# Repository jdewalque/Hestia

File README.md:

# Hestia

Bijou connecté avec bouton d'urgence : une pression envoie la position du
porteur par SMS à ses contacts. Prototype sur Thingy:91 X.

- `docs/architecture.md` — **à lire en premier** : architecture, fonctionnement
  et fonctionnalités, en résumé.
- `app/` — application mobile (Flutter, Android et iPhone) pour régler le bijou.
- `firmware/` — firmware du bijou pour le Thingy:91 X (voir `firmware/README.md`).
- `server/` — serveur qui transforme les alertes reçues par nRF Cloud en SMS
  (voir `server/README.md`).
- `docs/protocole-ble.md` — dialogue entre l'application et le bijou.
- `docs/consommation.md` — consommation estimée et autonomie du bijou.

## Application

L'application permet de relier le bijou au téléphone, de choisir les contacts
d'urgence, de saisir son nom et le message d'alerte, de voir l'état du bijou
(batterie, réseau mobile) et d'envoyer une alerte de test.

Les réglages sont enregistrés sur le téléphone puis envoyés au bijou dès qu'il
est à portée.

### Lancer l'application

Il faut [Flutter](https://docs.flutter.dev/get-started/install) et un téléphone
branché (le Bluetooth ne fonctionne pas sur émulateur).

```bash
cd app
flutter run
```

Sans bijou, le lien « Essayer sans bijou » de l'écran d'accueil lance un mode
démonstration avec un bijou simulé.

### Tests

```bash
cd app
flutter test
```

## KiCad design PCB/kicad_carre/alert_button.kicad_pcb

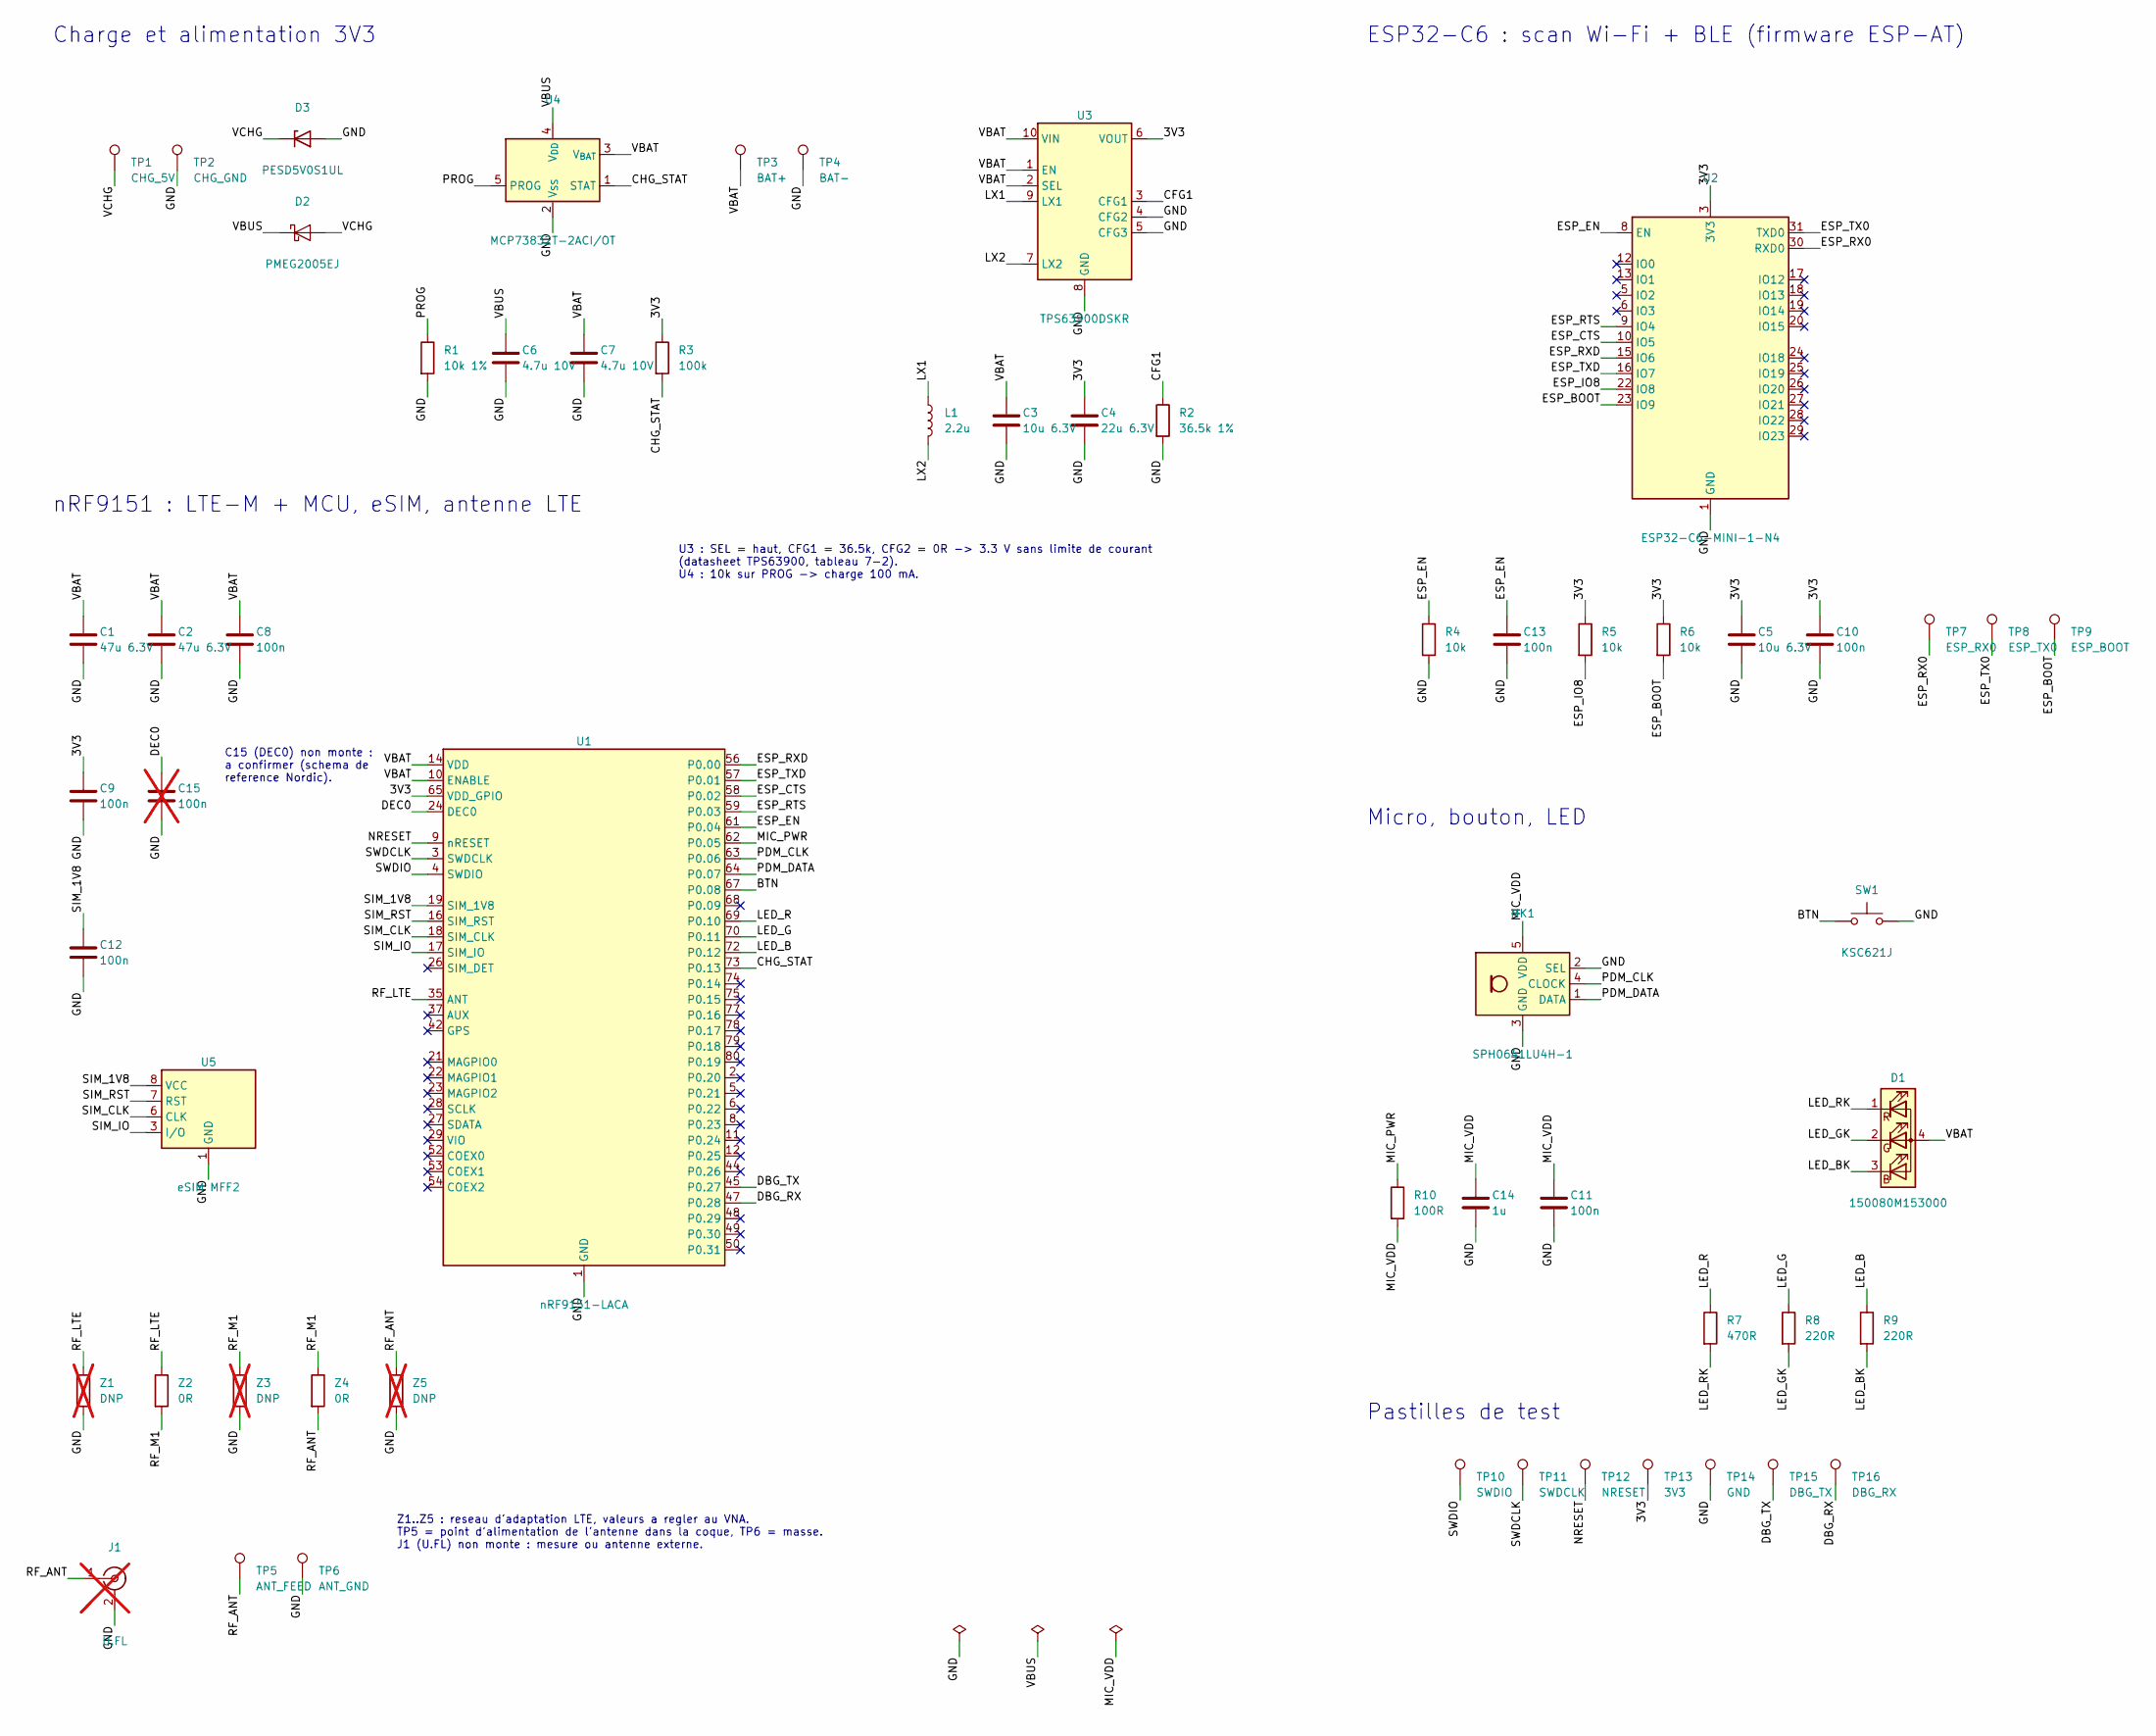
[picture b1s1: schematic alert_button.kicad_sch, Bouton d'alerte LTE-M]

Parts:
C1, C2: 47u 6.3V; C_0805_2012Metric; MPN GRM21BR60J476ME15
C3, C5: 10u 6.3V; C_0603_1608Metric
C4: 22u 6.3V; C_0805_2012Metric
C6, C7: 4.7u 10V; C_0603_1608Metric
C8, C9, C10, C11, C12, C13: 100n; C_0402_1005Metric
C14: 1u; C_0402_1005Metric
C15: 100n; C_0402_1005Metric; not fitted
D1: 150080M153000; LED_RGB_Wuerth_150080M153000; MPN 150080M153000
D2: PMEG2005EJ; D_SOD-323F; MPN PMEG2005EJ
D3: PESD5V0S1UL; D_SOD-882; MPN PESD5V0S1UL
J1: U.FL; U.FL_Hirose_U.FL-R-SMT-1_Vertical; MPN U.FL-R-SMT-1(10); not fitted
L1: 2.2u; L_Murata_DFE201610P; MPN DFE201612E-2R2M=P2
MK1: SPH0641LU4H-1; Knowles_LGA-5_3.5x2.65mm; MPN SPH0641LU4H-1
R1: 10k 1%; R_0402_1005Metric
R2: 36.5k 1%; R_0402_1005Metric
R3: 100k; R_0402_1005Metric
R4, R5, R6: 10k; R_0402_1005Metric
R7: 470R; R_0402_1005Metric
R8, R9: 220R; R_0402_1005Metric
R10: 100R; R_0402_1005Metric
SW1: KSC621J; SW_Push_1P1T_NO_CK_KSC6xxJ; MPN KSC621J LFS
TP1: CHG_5V; TestPoint_Pad_D2.0mm
TP2: CHG_GND; TestPoint_Pad_D2.0mm
TP3: BAT+; TestPoint_Pad_2.0x2.0mm
TP4: BAT-; TestPoint_Pad_2.0x2.0mm
TP5: ANT_FEED; TestPoint_Pad_1.5x1.5mm
TP6: ANT_GND; TestPoint_Pad_1.5x1.5mm
TP7: ESP_RX0; TestPoint_Pad_D1.0mm
TP8: ESP_TX0; TestPoint_Pad_D1.0mm
TP9: ESP_BOOT; TestPoint_Pad_D1.0mm
TP10: SWDIO; TestPoint_Pad_D1.0mm
TP11: SWDCLK; TestPoint_Pad_D1.0mm
TP12: NRESET; TestPoint_Pad_D1.0mm
TP13: 3V3; TestPoint_Pad_D1.0mm
TP14: GND; TestPoint_Pad_D1.0mm
TP15: DBG_TX; TestPoint_Pad_D1.0mm
TP16: DBG_RX; TestPoint_Pad_D1.0mm
U1: nRF9151-LACA; Nordic_nRF9151-LAxx_LGA-80-33EP_12.1x11.1mm_P0.5mm; MPN nRF9151-LACA-R7
U2: ESP32-C6-MINI-1-N4; ESP32-C6-MINI-1; MPN ESP32-C6-MINI-1-N4
U3: TPS63900DSKR; WSON-10-1EP_2.5x2.5mm_P0.5mm_EP1.2x2mm; MPN TPS63900DSKR
U4: MCP73832T-2ACI/OT; SOT-23-5; MPN MCP73832T-2ACI/OT
U5: eSIM MFF2; DFN-8-1EP_6x5mm_P1.27mm_EP2x2mm
Z1, Z3, Z5: DNP; R_0402_1005Metric; not fitted
Z2, Z4: 0R; R_0402_1005Metric

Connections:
/3V3: C4.1, C5.1, C9.1, C10.1, R3.1, R5.1, R6.1, TP13.1, U1.65 (VDD_GPIO), U2.3 (3V3), U3.6 (VOUT)
/BTN: SW1.1, U1.67 (P0.08)
/CFG1: R2.1, U3.3 (CFG1)
/CHG_STAT: R3.2, U1.73 (P0.13), U4.1 (STAT)
/DBG_RX: TP16.1, U1.47 (P0.28)
/DBG_TX: TP15.1, U1.45 (P0.27)
/DEC0: C15.1, U1.24 (DEC0)
/ESP_BOOT: R6.2, TP9.1, U2.23 (IO9)
/ESP_CTS: U1.58 (P0.02), U2.10 (IO5)
/ESP_EN: C13.1, R4.1, U1.61 (P0.04), U2.8 (EN)
/ESP_IO8: R5.2, U2.22 (IO8)
/ESP_RTS: U1.59 (P0.03), U2.9 (IO4)
/ESP_RX0: TP7.1, U2.30 (RXD0)
/ESP_RXD: U1.56 (P0.00), U2.15 (IO6)
/ESP_TX0: TP8.1, U2.31 (TXD0)
/ESP_TXD: U1.57 (P0.01), U2.16 (IO7)
/GND: C1.2, C2.2, C3.2, C4.2, C5.2, C6.2, C7.2, C8.2, C9.2, C10.2, C11.2, C12.2, C13.2, C14.2, C15.2, D3.2 (A), J1.2 (Ext), MK1.2 (SEL), MK1.3 (GND), R1.2, R2.2, R4.2, SW1.2, TP2.1, TP4.1, TP6.1, TP14.1, U1.1 (GND), U1.7 (GND), U1.13 (GND), U1.15 (GND), U1.20 (GND), U1.25 (GND), U1.30 (GND), U1.34 (GND), U1.36 (GND), U1.38 (GND), U1.39 (GND), U1.40 (GND), U1.41 (GND), U1.43 (GND), U1.46 (GND), U1.51 (GND), U1.55 (GND), U1.60 (GND), U1.66 (GND), U1.71 (GND), U1.76 (GND), U1.105 (GND), U1.106 (GND), U1.107 (GND), U1.108 (GND), U1.109 (GND), U1.110 (GND), U1.111 (GND), U1.112 (GND), U1.113 (GND), U2.1 (GND), U2.2 (GND), U2.11 (GND), U2.14 (GND), U2.36 (GND), U2.37 (GND), U2.38 (GND), U2.39 (GND), U2.40 (GND), U2.41 (GND), U2.42 (GND), U2.43 (GND), U2.44 (GND), U2.45 (GND), U2.46 (GND), U2.47 (GND), U2.48 (GND), U2.49 (GND), U2.50 (GND), U2.51 (GND), U2.52 (GND), U2.53 (GND), U3.4 (CFG2), U3.5 (CFG3), U3.8 (GND), U3.11 (GND), U4.2 (V_{SS}), U5.1 (GND), Z1.2, Z3.2, Z5.2
/LED_B: R9.1, U1.72 (P0.12)
/LED_BK: D1.3 (BK), R9.2
/LED_G: R8.1, U1.70 (P0.11)
/LED_GK: D1.2 (GK), R8.2
/LED_R: R7.1, U1.69 (P0.10)
/LED_RK: D1.1 (RK), R7.2
/LX1: L1.1, U3.9 (LX1)
/LX2: L1.2, U3.7 (LX2)
/MIC_PWR: R10.1, U1.62 (P0.05)
/MIC_VDD: C11.1, C14.1, MK1.5 (VDD), R10.2
/NRESET: TP12.1, U1.9 (nRESET)
/PDM_CLK: MK1.4 (CLOCK), U1.63 (P0.06)
/PDM_DATA: MK1.1 (DATA), U1.64 (P0.07)
/PROG: R1.1, U4.5 (PROG)
/RF_ANT: J1.1 (In), TP5.1, Z4.2, Z5.1
/RF_LTE: U1.35 (ANT), Z1.1, Z2.1
/RF_M1: Z2.2, Z3.1, Z4.1
/SIM_1V8: C12.1, U1.19 (SIM_1V8), U5.8 (VCC)
/SIM_CLK: U1.18 (SIM_CLK), U5.6 (CLK)
/SIM_IO: U1.17 (SIM_IO), U5.3 (I/O)
/SIM_RST: U1.16 (SIM_RST), U5.7 (RST)
/SWDCLK: TP11.1, U1.3 (SWDCLK)
/SWDIO: TP10.1, U1.4 (SWDIO)
/VBAT: C1.1, C2.1, C3.1, C7.1, C8.1, D1.4 (A), TP3.1, U1.10 (ENABLE), U1.14 (VDD), U3.1 (EN), U3.2 (SEL), U3.10 (VIN), U4.3 (V_{BAT})
/VBUS: C6.1, D2.1 (K), U4.4 (V_{DD})
/VCHG: D2.2 (A), D3.1 (K), TP1.1

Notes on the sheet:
Charge et alimentation 3V3
nRF9151 : LTE-M + MCU, eSIM, antenne LTE
ESP32-C6 : scan Wi-Fi + BLE (firmware ESP-AT)
Micro, bouton, LED
Pastilles de test
Z1..Z5 : reseau d'adaptation LTE, valeurs a regler au VNA. TP5 = point d'alimentation de l'antenne dans la coque, TP6 = masse. J1 (U.FL) non monte : mesure ou antenne externe.
U3 : SEL = haut, CFG1 = 36.5k, CFG2 = 0R -> 3.3 V sans limite de courant (datasheet TPS63900, tableau 7-2). U4 : 10k sur PROG -> charge 100 mA.
C15 (DEC0) non monte : a confirmer (schema de reference Nordic).

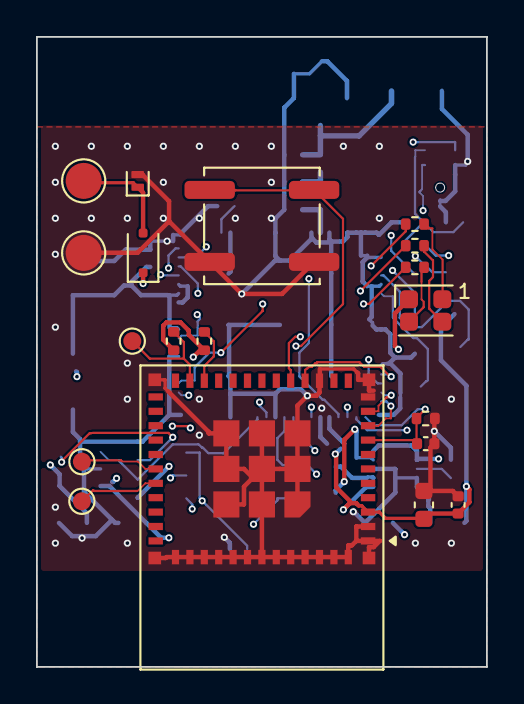
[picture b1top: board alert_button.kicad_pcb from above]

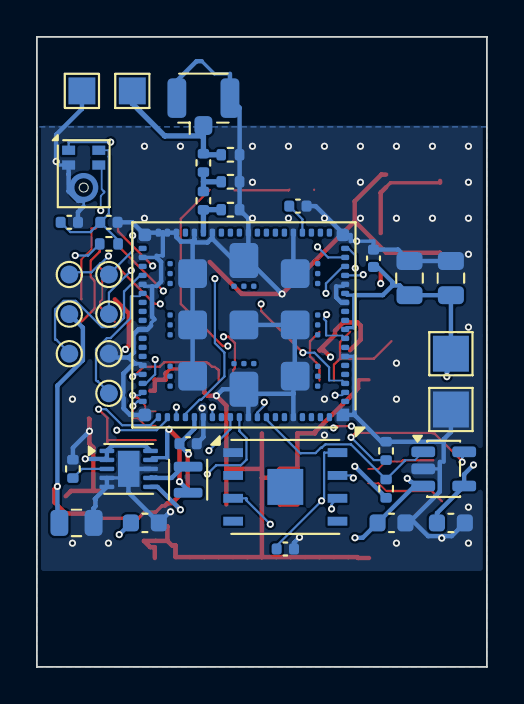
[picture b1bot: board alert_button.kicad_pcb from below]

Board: 4 copper layers, 25.0 x 35.0 mm, 58 parts (39 on the bottom side), 43 nets.

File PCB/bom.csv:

Refs,Qty,Value,MPN,Footprint,Mounted
C1 C2,2,47u 6.3V,GRM21BR60J476ME15,C_0805_2012Metric,yes
C3 C5,2,10u 6.3V,,C_0603_1608Metric,yes
C4,1,22u 6.3V,,C_0805_2012Metric,yes
C6 C7,2,4.7u 10V,,C_0603_1608Metric,yes
C8 C9 C10 C11 C12 C13,6,100n,,C_0402_1005Metric,yes
C14,1,1u,,C_0402_1005Metric,yes
C15,1,100n,,C_0402_1005Metric,no
D1,1,150080M153000,150080M153000,LED_RGB_Wuerth_150080M153000,yes
D2,1,PMEG2005EJ,PMEG2005EJ,D_SOD-323F,yes
D3,1,PESD5V0S1UL,PESD5V0S1UL,D_SOD-882,yes
J1,1,U.FL,U.FL-R-SMT-1(10),U.FL_Hirose_U.FL-R-SMT-1_Vertical,no
L1,1,2.2u,DFE201612E-2R2M=P2,L_Murata_DFE201610P,yes
MK1,1,SPH0641LU4H-1,SPH0641LU4H-1,Knowles_LGA-5_3.5x2.65mm,yes
R1,1,10k 1%,,R_0402_1005Metric,yes
R2,1,36.5k 1%,,R_0402_1005Metric,yes
R3,1,100k,,R_0402_1005Metric,yes
R4 R5 R6,3,10k,,R_0402_1005Metric,yes
R7,1,470R,,R_0402_1005Metric,yes
R8 R9,2,220R,,R_0402_1005Metric,yes
R10,1,100R,,R_0402_1005Metric,yes
SW1,1,KSC621J,KSC621J LFS,SW_Push_1P1T_NO_CK_KSC6xxJ,yes
U1,1,nRF9151-LACA,nRF9151-LACA-R7,Nordic_nRF9151-LAxx_LGA-80-33EP_12.1x11.1mm_P0.5mm,yes
U2,1,ESP32-C6-MINI-1-N4,ESP32-C6-MINI-1-N4,ESP32-C6-MINI-1,yes
U3,1,TPS63900DSKR,TPS63900DSKR,WSON-10-1EP_2.5x2.5mm_P0.5mm_EP1.2x2mm,yes
U4,1,MCP73832T-2ACI/OT,MCP73832T-2ACI/OT,SOT-23-5,yes
U5,1,eSIM MFF2,,DFN-8-1EP_6x5mm_P1.27mm_EP2x2mm,yes
Z1 Z3 Z5,3,DNP,,R_0402_1005Metric,no
Z2 Z4,2,0R,,R_0402_1005Metric,yes
